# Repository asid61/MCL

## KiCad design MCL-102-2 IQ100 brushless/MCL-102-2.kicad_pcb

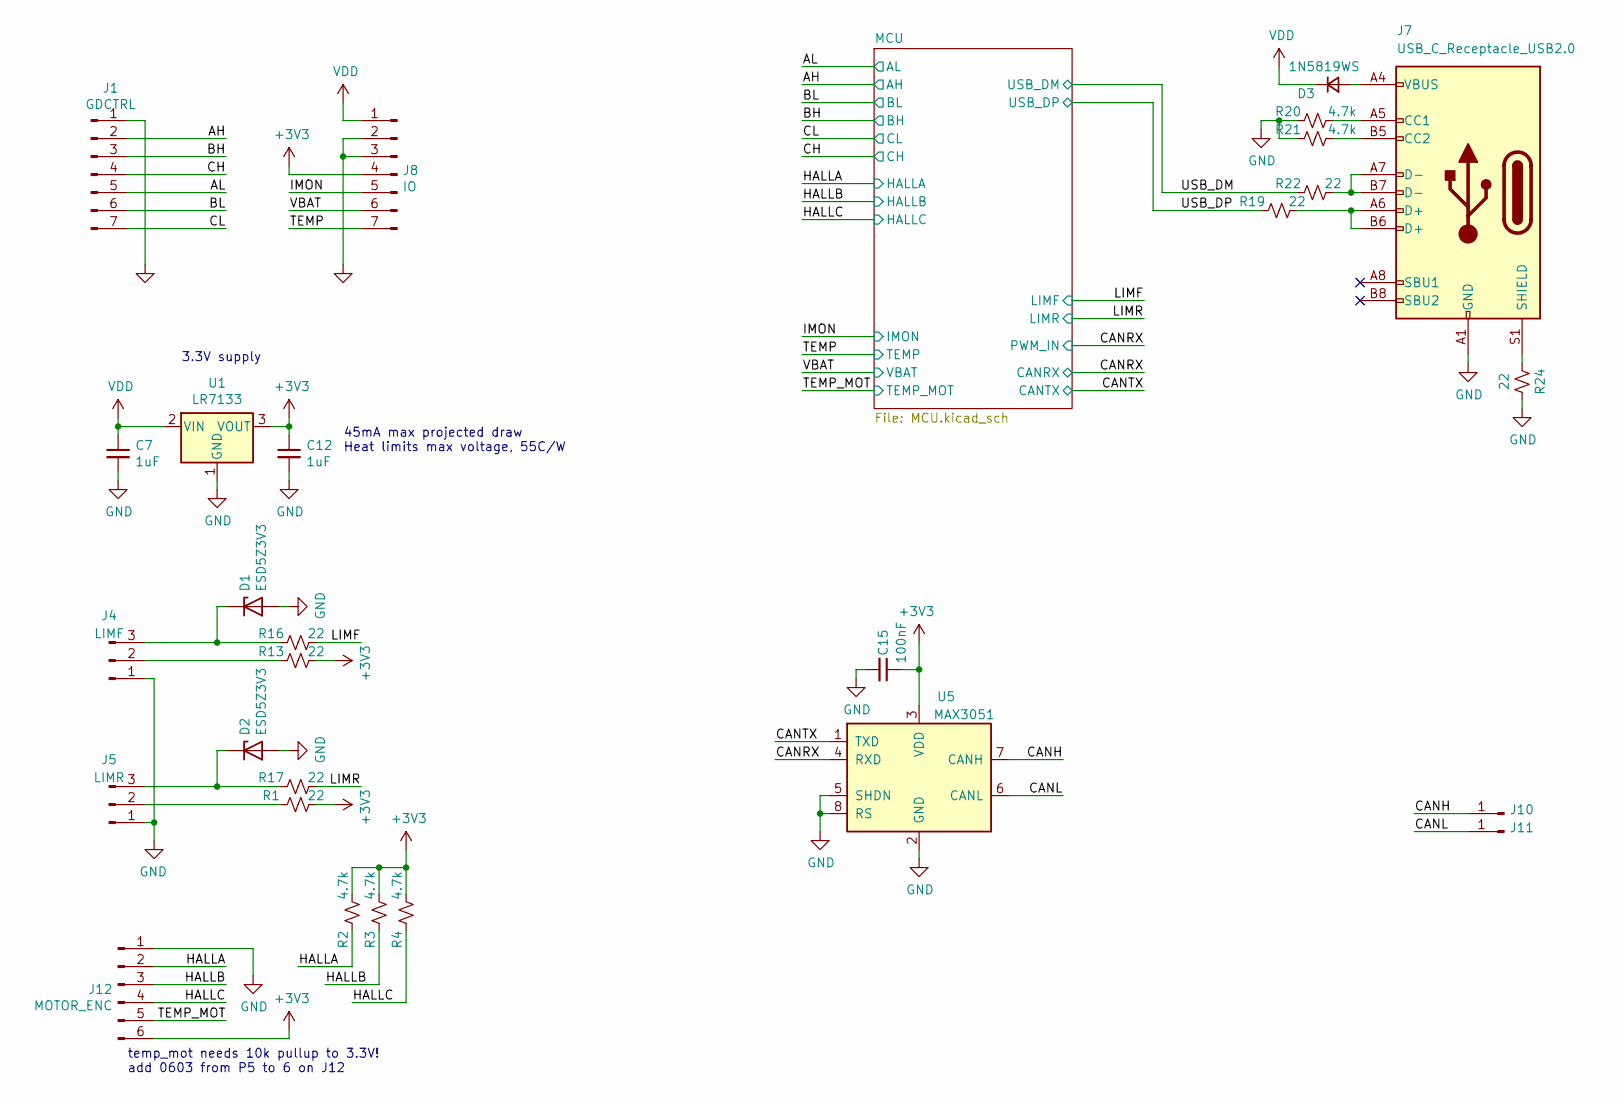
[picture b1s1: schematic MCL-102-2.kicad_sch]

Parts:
C7, C12: 1uF; C_0603_1608Metric; LCSC C15849
C15: 100nF; C_0402_1005Metric
D1, D2: ESD5Z3V3; D_SOD-523; LCSC C502545
D3: 1N5819WS; D_SOD-323; LCSC C191023
J1: GDCTRL; PinSocket_1x07_P2.54mm_Vertical; LCSC C492406
J4: LIMF; PinHeader_1x03_P2.54mm_Horizontal
J5: LIMR; PinHeader_1x03_P2.54mm_Horizontal
J7: USB_C_Receptacle_USB2.0; USB_C_Receptacle_HRO_TYPE-C-31-M-12; LCSC C165948
J8: IO; PinSocket_1x07_P2.54mm_Vertical; LCSC C492406
J10, J11: Conn_01x01_Male; SOLDERPAD_100x200
J12: MOTOR_ENC; JST_PH_S6B-PH-SM4-TB_1x06-1MP_P2.00mm_Horizontal; LCSC C146050
R1, R13, R16, R17, R19, R22, R24: 22; R_0402_1005Metric
R2, R3, R4, R20, R21: 4.7k; R_0402_1005Metric
U1: LR7133; SOT-89-3; LCSC C914127
U5: MAX3051; SOT-23-8; LCSC C112005

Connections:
+3V3: C12.1, C15.1, J8.4, J12.6, R1.2, R2.1, R3.1, R4.1, R13.2, U1.3 (VOUT), U5.3 (VDD); also elsewhere on the board
/AH: J1.2; also elsewhere on the board
/AL: J1.5; also elsewhere on the board
/BH: J1.3; also elsewhere on the board
/BL: J1.6; also elsewhere on the board
/CANH: J10.1, U5.7 (CANH)
/CANL: J11.1, U5.6 (CANL)
/CANRX: U5.4 (RXD); also elsewhere on the board
/CANTX: U5.1 (TXD); also elsewhere on the board
/CH: J1.4; also elsewhere on the board
/CL: J1.7; also elsewhere on the board
/HALLA: J12.2, R2.2; also elsewhere on the board
/HALLB: J12.3, R3.2; also elsewhere on the board
/HALLC: J12.4, R4.2; also elsewhere on the board
/IMON: J8.5; also elsewhere on the board
/LIMF: R16.2; also elsewhere on the board
/LIMR: R17.2; also elsewhere on the board
/TEMP: J8.7; also elsewhere on the board
/TEMP_MOT: J12.5; also elsewhere on the board
/USB_DM: R22.1; also elsewhere on the board
/USB_DP: R19.1; also elsewhere on the board
/VBAT: J8.6; also elsewhere on the board
GND: C7.2, C12.2, C15.2, D1.2 (A), D2.2 (A), J1.1, J4.1, J5.1, J7.A1 (GND), J7.A12 (GND), J7.B1 (GND), J7.B12 (GND), J8.2, J8.3, J12.1, R20.2, R21.2, R24.1, U1.1 (GND), U5.2 (GND), U5.5 (SHDN), U5.8 (RS); also elsewhere on the board
unnamed: D1.1 (K), J4.3, R16.1
unnamed: D2.1 (K), J5.3, R17.1
unnamed: D3.2 (A), J7.A4 (VBUS), J7.A9 (VBUS), J7.B4 (VBUS), J7.B9 (VBUS)
unnamed: J4.2, R13.1
unnamed: J5.2, R1.1
unnamed: J7.A5 (CC1), R20.1
unnamed: J7.A6 (D+), J7.B6 (D+), R19.2
unnamed: J7.A7 (D-), J7.B7 (D-), R22.2
unnamed: J7.B5 (CC2), R21.1
unnamed: J7.S1 (SHIELD), R24.2
VDD: C7.1, D3.1 (K), J8.1, U1.2 (VIN)

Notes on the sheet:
temp_mot needs 10k pullup to 3.3V! add 0603 from P5 to 6 on J12
3.3V supply
45mA max projected draw Heat limits max voltage, 55C/W

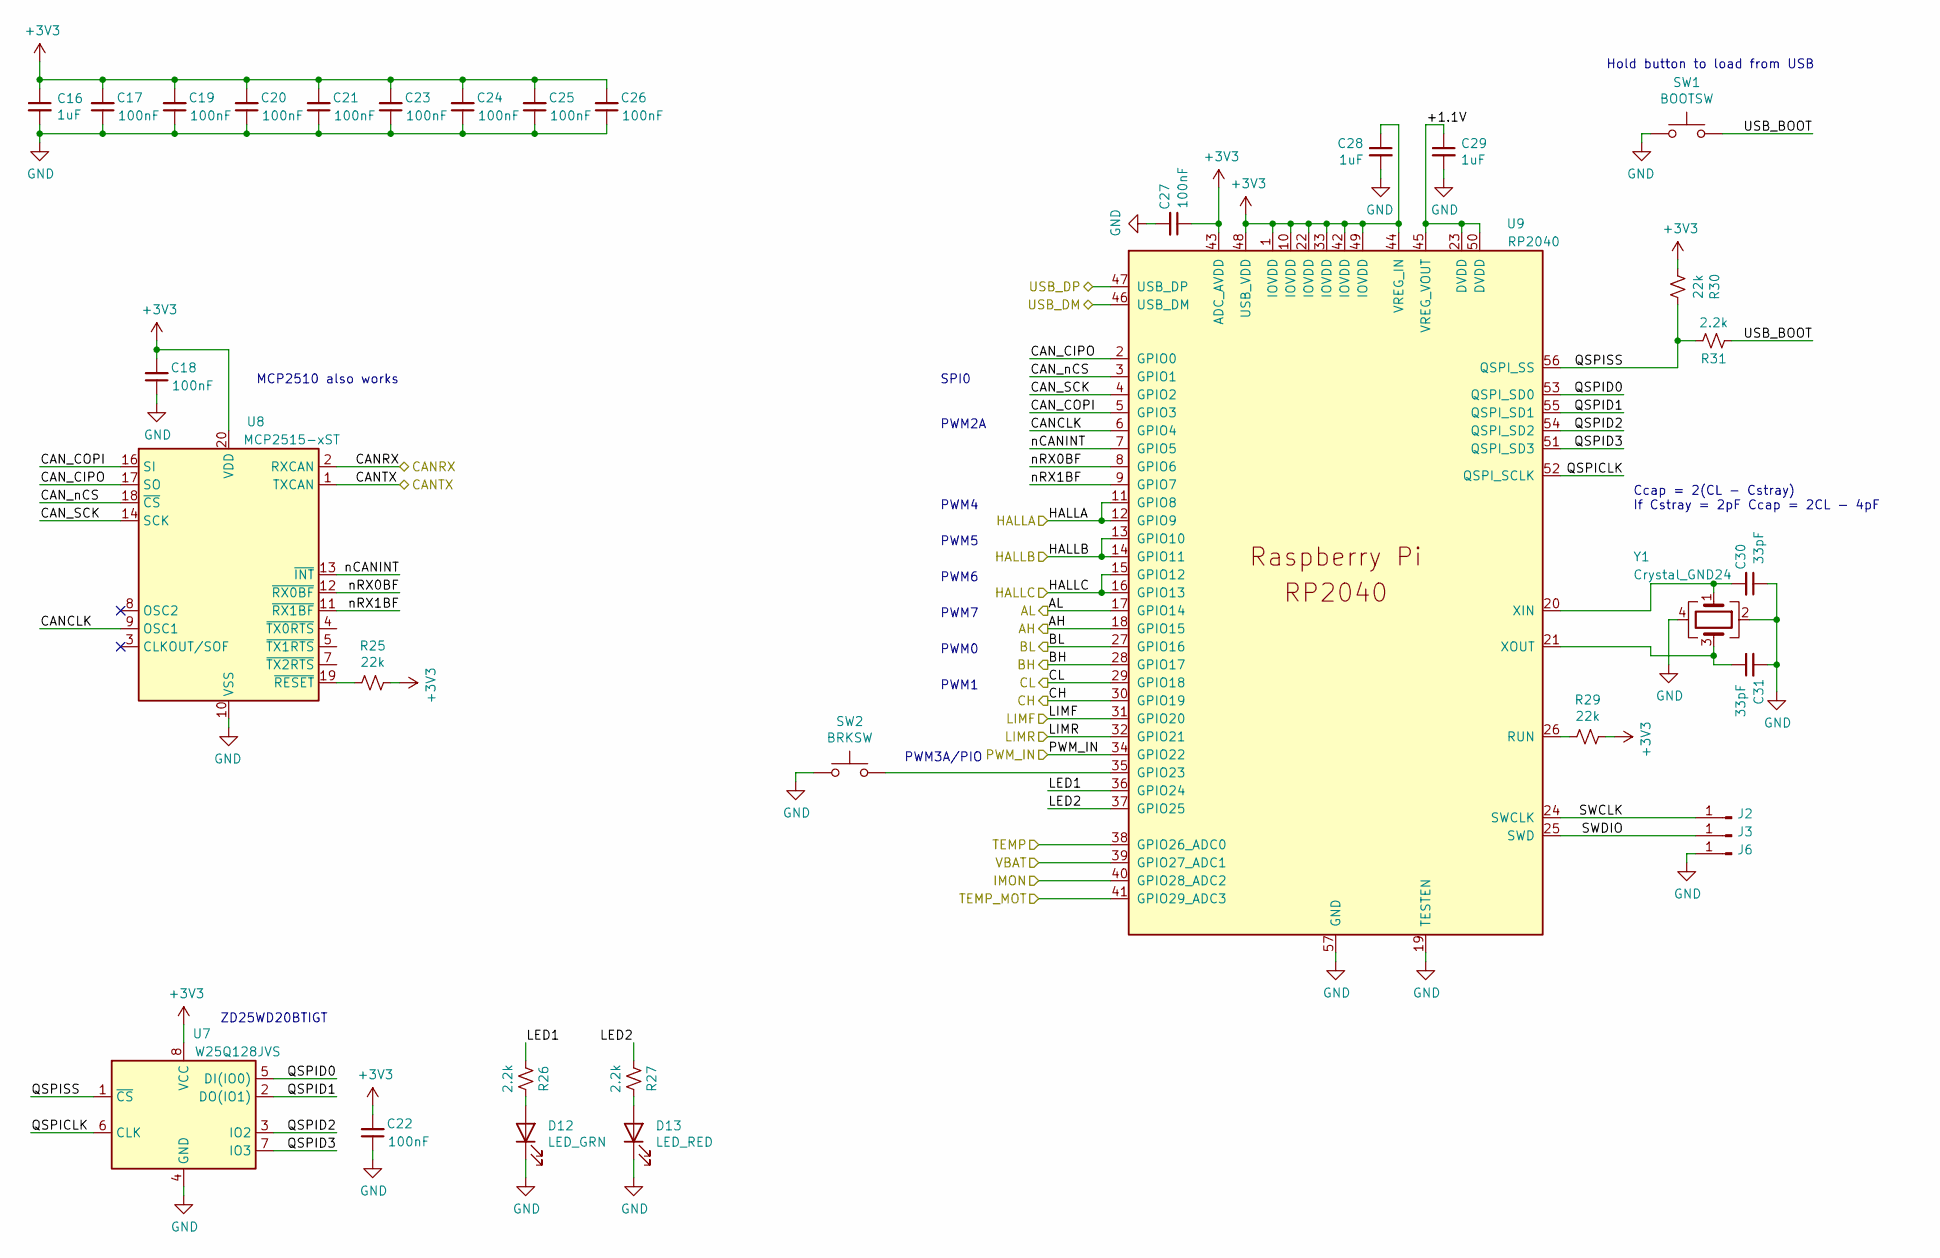
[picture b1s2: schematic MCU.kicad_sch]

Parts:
C16, C28, C29: 1uF; C_0603_1608Metric; LCSC C15849
C17, C18, C19, C20, C21, C22, C23, C24, C25, C26, C27: 100nF; C_0402_1005Metric
C30, C31: 33pF; C_0402_1005Metric
D12: LED_GRN; D_0603_1608Metric
D13: LED_RED; D_0603_1608Metric
J2, J3, J6: Conn_01x01_Male; SOLDERPAD_100x200
R25, R29, R30: 22k; R_0402_1005Metric
R26, R27, R31: 2.2k; R_0402_1005Metric
SW1: BOOTSW; SW_PUSH_6mm_H4.3mm; LCSC C2837531
SW2: BRKSW; SW_PUSH_6mm_H4.3mm; LCSC C2837531
U7: W25Q128JVS; SOIC-8_5.23x5.23mm_P1.27mm; LCSC C97521
U8: MCP2515-xST; TSSOP-20_4.4x6.5mm_P0.65mm; LCSC C185941
U9: RP2040; RP2040-QFN-56; LCSC C2040
Y1: Crystal_GND24; Crystal_SMD_3225-4Pin_3.2x2.5mm; LCSC C9002

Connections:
+3V3: C16.1, C17.2, C18.2, C19.2, C20.2, C21.2, C22.2, C23.2, C24.2, C25.2, C26.2, C27.1, C28.1, R25.2, R29.2, R30.1, U7.8 (VCC), U8.20 (VDD), U9.1 (IOVDD), U9.10 (IOVDD), U9.22 (IOVDD), U9.33 (IOVDD), U9.42 (IOVDD), U9.43 (ADC_AVDD), U9.44 (VREG_IN), U9.48 (USB_VDD), U9.49 (IOVDD); also elsewhere on the board
/AH: U9.18 (GPIO15); also elsewhere on the board
/AL: U9.17 (GPIO14); also elsewhere on the board
/BH: U9.28 (GPIO17); also elsewhere on the board
/BL: U9.27 (GPIO16); also elsewhere on the board
/CANRX: U8.2 (RXCAN), U9.34 (GPIO22); also elsewhere on the board
/CANTX: U8.1 (TXCAN); also elsewhere on the board
/CH: U9.30 (GPIO19); also elsewhere on the board
/CL: U9.29 (GPIO18); also elsewhere on the board
/HALLA: U9.11 (GPIO8), U9.12 (GPIO9); also elsewhere on the board
/HALLB: U9.13 (GPIO10), U9.14 (GPIO11); also elsewhere on the board
/HALLC: U9.15 (GPIO12), U9.16 (GPIO13); also elsewhere on the board
/IMON: U9.40 (GPIO28_ADC2); also elsewhere on the board
/LIMF: U9.31 (GPIO20); also elsewhere on the board
/LIMR: U9.32 (GPIO21); also elsewhere on the board
/MCU/+1.1V: C29.1, U9.23 (DVDD), U9.45 (VREG_VOUT), U9.50 (DVDD)
/MCU/CANCLK: U8.9 (OSC1), U9.6 (GPIO4)
/MCU/CAN_CIPO: U8.17 (SO), U9.2 (GPIO0)
/MCU/CAN_COPI: U8.16 (SI), U9.5 (GPIO3)
/MCU/CAN_SCK: U8.14 (SCK), U9.4 (GPIO2)
/MCU/CAN_nCS: U8.18 (~CS), U9.3 (GPIO1)
/MCU/LED1: R26.2, U9.36 (GPIO24)
/MCU/LED2: R27.2, U9.37 (GPIO25)
/MCU/QSPICLK: U7.6 (CLK), U9.52 (QSPI_SCLK)
/MCU/QSPID0: U7.5 (DI(IO0)), U9.53 (QSPI_SD0)
/MCU/QSPID1: U7.2 (DO(IO1)), U9.55 (QSPI_SD1)
/MCU/QSPID2: U7.3 (IO2), U9.54 (QSPI_SD2)
/MCU/QSPID3: U7.7 (IO3), U9.51 (QSPI_SD3)
/MCU/QSPISS: R30.2, R31.1, U7.1 (~CS), U9.56 (QSPI_SS)
/MCU/SWCLK: J2.1, U9.24 (SWCLK)
/MCU/SWDIO: J3.1, U9.25 (SWD)
/MCU/USB_BOOT: R31.2, SW1.2
/MCU/nCANINT: U8.13 (~INT), U9.7 (GPIO5)
/MCU/nRX0BF: U8.12 (~RX0BF), U9.8 (GPIO6)
/MCU/nRX1BF: U8.11 (~RX1BF), U9.9 (GPIO7)
/TEMP: U9.38 (GPIO26_ADC0); also elsewhere on the board
/TEMP_MOT: U9.41 (GPIO29_ADC3); also elsewhere on the board
/USB_DM: U9.46 (USB_DM); also elsewhere on the board
/USB_DP: U9.47 (USB_DP); also elsewhere on the board
/VBAT: U9.39 (GPIO27_ADC1); also elsewhere on the board
GND: C16.2, C17.1, C18.1, C19.1, C20.1, C21.1, C22.1, C23.1, C24.1, C25.1, C26.1, C27.2, C28.2, C29.2, C30.1, C31.2, D12.1 (K), D13.1 (K), J6.1, SW1.1, SW2.1, U7.4 (GND), U8.10 (VSS), U9.19 (TESTEN), U9.57 (GND), Y1.2, Y1.4; also elsewhere on the board
unnamed: C30.2, U9.20 (XIN), Y1.1
unnamed: C31.1, U9.21 (XOUT), Y1.3
unnamed: D12.2 (A), R26.1
unnamed: D13.2 (A), R27.1
unnamed: R25.1, U8.19 (~RESET)
unnamed: R29.1, U9.26 (RUN)
unnamed: SW2.2, U9.35 (GPIO23)

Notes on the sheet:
Hold button to load from USB
PWM5
PWM7
PWM1
PWM3A/PIO
MCP2510 also works
PWM2A
Ccap = 2(CL - Cstray) If Cstray = 2pF Ccap = 2CL - 4pF
PWM6
ZD25WD20BTIGT
SPI0
PWM0
PWM4

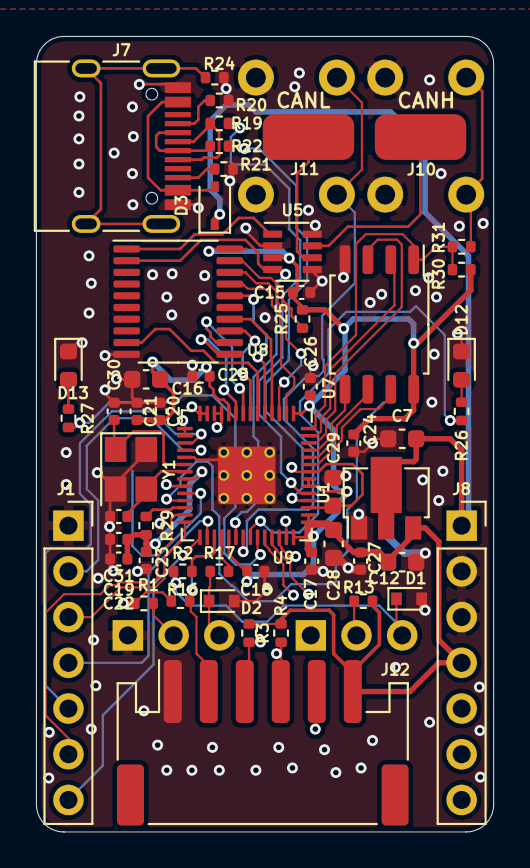
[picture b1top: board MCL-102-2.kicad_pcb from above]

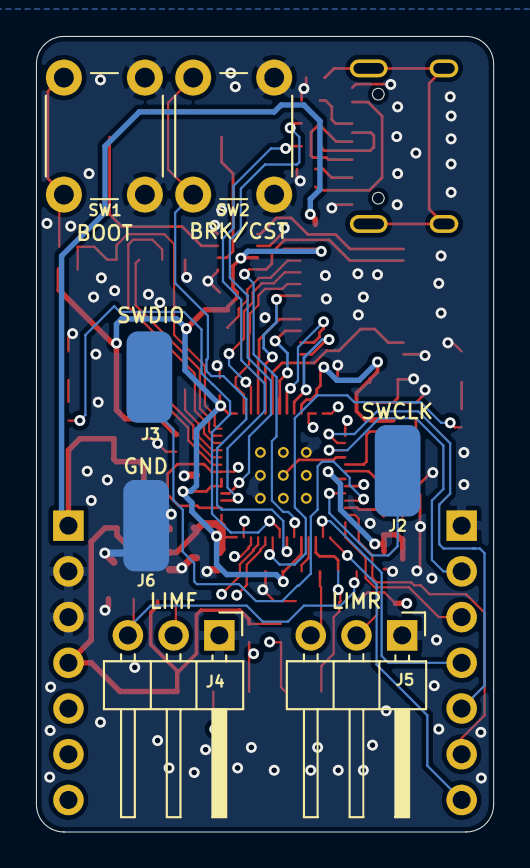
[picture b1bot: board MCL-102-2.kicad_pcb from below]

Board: 4 copper layers, 25.4 x 44.2 mm, 61 parts (7 on the bottom side), 61 nets.

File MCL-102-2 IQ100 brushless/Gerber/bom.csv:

Comment,Designator,Footprint,LCSC
"1uF","C7,C12,C16,C28,C29","Capacitor_SMD:C_0603_1608Metric","C15849"
"100nF","C15,C17,C18,C19,C20,C21,C22,C23,C24,C25,C26,C27","Capacitor_SMD:C_0402_1005Metric",""
"33pF","C30,C31","Capacitor_SMD:C_0402_1005Metric",""
"ESD5Z3V3","D1,D2","Diode_SMD:D_SOD-523","C502545"
"LED_GRN","D12","Diode_SMD:D_0603_1608Metric",""
"LED_RED","D13","Diode_SMD:D_0603_1608Metric",""
"1N5819WS","D3","Diode_SMD:D_SOD-323","C191023"
"GDCTRL","J1","Connector_PinSocket_2.54mm:PinSocket_1x07_P2.54mm_Vertical","C492406"
"Conn_01x01_Male","J2,J3,J6,J10,J11","Anand_parts:SOLDERPAD_100x200",""
"MOTOR_ENC","J12","Connector_JST:JST_PH_S6B-PH-SM4-TB_1x06-1MP_P2.00mm_Horizontal","C146050"
"LIMF","J4","Connector_PinHeader_2.54mm:PinHeader_1x03_P2.54mm_Horizontal",""
"LIMR","J5","Connector_PinHeader_2.54mm:PinHeader_1x03_P2.54mm_Horizontal",""
"USB_C_Receptacle_USB2.0","J7","Connector_USB:USB_C_Receptacle_HRO_TYPE-C-31-M-12","C165948"
"IO","J8","Connector_PinSocket_2.54mm:PinSocket_1x07_P2.54mm_Vertical","C492406"
"4.7k","R2,R3,R4,R20,R21","Resistor_SMD:R_0402_1005Metric",""
"22","R1,R13,R16,R17,R19,R22,R24","Resistor_SMD:R_0402_1005Metric",""
"2.2k","R26,R27,R31","Resistor_SMD:R_0402_1005Metric",""
"22k","R25,R29,R30","Resistor_SMD:R_0402_1005Metric",""
"BOOTSW","SW1","Button_Switch_THT:SW_PUSH_6mm_H4.3mm","C2837531"
"BRKSW","SW2","Button_Switch_THT:SW_PUSH_6mm_H4.3mm","C2837531"
"LR7133","U1","Package_TO_SOT_SMD:SOT-89-3","C914127"
"MAX3051","U5","Package_TO_SOT_SMD:SOT-23-8","C112005"
"W25Q128JVS","U7","Package_SO:SOIC-8_5.23x5.23mm_P1.27mm","C97521"
"MCP2515-xST","U8","Package_SO:TSSOP-20_4.4x6.5mm_P0.65mm","C185941"
"RP2040","U9","MCU_RaspberryPi_and_Boards:RP2040-QFN-56","C2040"
"Crystal_GND24","Y1","Crystal:Crystal_SMD_3225-4Pin_3.2x2.5mm","C9002"

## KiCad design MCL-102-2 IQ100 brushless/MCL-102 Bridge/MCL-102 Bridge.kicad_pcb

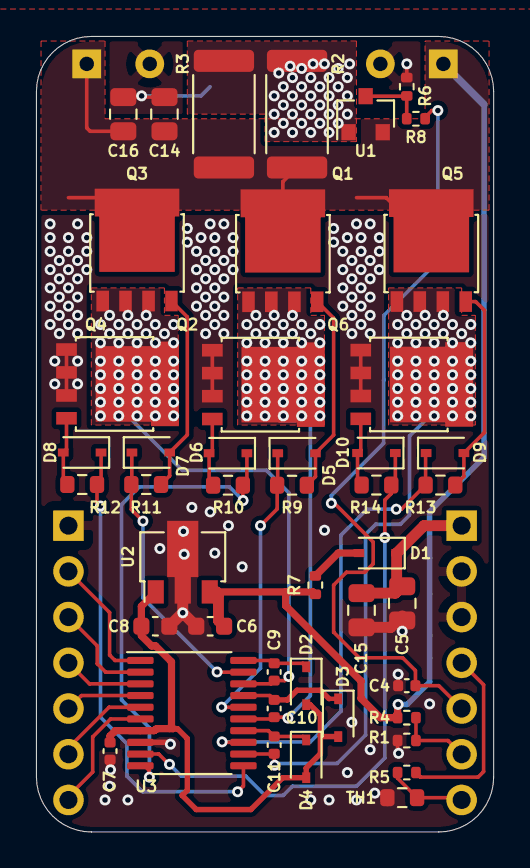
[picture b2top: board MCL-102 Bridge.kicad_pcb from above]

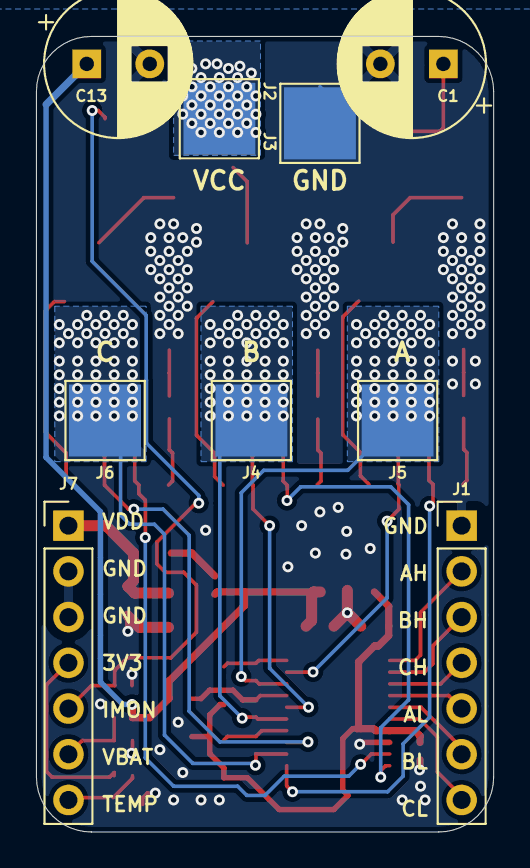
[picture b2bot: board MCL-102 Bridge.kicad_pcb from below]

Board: 4 copper layers, 25.4 x 44.2 mm, 54 parts (9 on the bottom side), 35 nets.

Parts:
C1, C13: 680uF; CP_Radial_D8.0mm_P3.50mm
C4, C7, C9, C10, C11: 100nF; C_0402_1005Metric
C5, C14, C15, C16: 22uF; C_0805_2012Metric
C6, C8: 1uF; C_0603_1608Metric
D1, D2, D3, D4, D5, D6, D7, D8, D9, D10: 1N4148WS; D_SOD-323
J1: GDCTRL; PinHeader_1x07_P2.54mm_Vertical
J2, J3, J4, J5, J6: Conn_01x01_Male; TestPoint_Pad_4.0x4.0mm
J7: IO; PinHeader_1x07_P2.54mm_Vertical
Q1, Q2, Q3, Q4, Q5, Q6: HYG013N03LS1C2; LFPAK56
R1: 4.7k; R_0402_1005Metric
R2, R3: 0.001; R_2512_6332Metric
R4: 22k; R_0402_1005Metric
R5, R6, R8: 2.2k; R_0402_1005Metric
R7: 22; R_0402_1005Metric
R9, R10, R11, R12, R13, R14: 1; R_0603_1608Metric
TH1: 10k; R_0603_1608Metric
U1: ZXCT1009F; SOT-23
U2: L78L12_SOT89; SOT-89-3
U3: EG2133; TSSOP-20_4.4x6.5mm_P0.65mm

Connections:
+3V3: J7.4, R1.2
+12V: C7.2, C8.1, D2.2 (A), D3.2 (A), D4.2 (A), U2.1 (OUT), U3.7 (VCC)
/AH: J1.2, U3.1 (HIN1)
/AHO: D7.1 (K), R11.1, U3.19 (HO1)
/AL: J1.5, U3.4 (~LIN1)
/ALO: D8.1 (K), R12.1, U3.11 (LO1)
/BH: J1.3, U3.2 (HIN2)
/BHO: D5.1 (K), R9.1, U3.16 (HO2)
/BL: J1.6, U3.5 (~LIN2)
/BLO: D6.1 (K), R10.1, U3.10 (LO2)
/CH: J1.4, U3.3 (HIN3)
/CHO: D9.1 (K), R13.1, U3.13 (HO3)
/CL: J1.7, U3.6 (~LIN3)
/CLO: D10.1 (K), R14.1, U3.9 (LO3)
/IMON: C4.2, J7.5, R8.2
/MA: C9.1, J5.1, Q3.1 (S), Q3.2 (S), Q3.3 (S), Q4.5 (D), U3.18 (VS1)
/MB: C10.1, J4.1, Q1.1 (S), Q1.2 (S), Q1.3 (S), Q2.5 (D), U3.15 (VS2)
/MC: C11.1, J6.1, Q5.1 (S), Q5.2 (S), Q5.3 (S), Q6.5 (D), U3.12 (VS3)
/PHASEA/HD: D5.2 (A), Q1.4 (G), R9.2
/PHASEA/LD: D6.2 (A), Q2.4 (G), R10.2
/PHASEB/HD: D7.2 (A), Q3.4 (G), R11.2
/PHASEB/LD: D8.2 (A), Q4.4 (G), R12.2
/Temp: J7.7, R1.1, TH1.1
/VBAT: J7.6, R4.2, R5.1
/sheet6191AFC6/HD: D9.2 (A), Q5.4 (G), R13.2
/sheet6191AFC6/LD: D10.2 (A), Q6.4 (G), R14.2
GND: C1.2, C4.1, C5.2, C6.2, C7.1, C8.2, C13.2, C14.2, C15.2, C16.2, J1.1, J3.1, J7.2, J7.3, Q2.1 (S), Q2.2 (S), Q2.3 (S), Q4.1 (S), Q4.2 (S), Q4.3 (S), Q6.1 (S), Q6.2 (S), Q6.3 (S), R5.2, R6.2, TH1.2, U2.2 (GND), U3.8 (GND)
unnamed: C9.2, D2.1 (K), U3.20 (VB1)
unnamed: C10.2, D3.1 (K), U3.17 (VB2)
unnamed: C11.2, D4.1 (K), U3.14 (VB3)
unnamed: D1.2 (A), R7.2
unnamed: J2.1, R2.1, R3.1, U1.1 (Vs-)
unnamed: R6.1, R8.1, U1.3 (Iout)
VCC: C1.1, C6.1, C13.1, C14.1, C16.1, Q1.5 (D), Q3.5 (D), Q5.5 (D), R2.2, R3.2, R4.1, R7.1, U1.2 (Vs+), U2.3 (IN)
VDD: C5.1, C15.1, D1.1 (K), J7.1

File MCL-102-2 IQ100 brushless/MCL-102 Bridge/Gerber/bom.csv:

Comment,Designator,Footprint,LCSC
"680uF","C1,C13","Capacitor_THT:CP_Radial_D8.0mm_P3.50mm","C442829"
"100nF","C4,C7,C9,C10,C11","Capacitor_SMD:C_0402_1005Metric",""
"22uF","C5,C14,C15,C16","Capacitor_SMD:C_0805_2012Metric","C45783"
"1uF","C6,C8","Capacitor_SMD:C_0603_1608Metric","C15849"
"1N4148WS","D1,D2,D3,D4,D5,D6,D7,D8,D9,D10","Diode_SMD:D_SOD-323","C2128"
"Conn_01x08_Male","IO1","Connector_PinHeader_2.54mm:PinHeader_1x07_P2.54mm_Vertical",""
"GDCTRL","J1","Connector_PinHeader_2.54mm:PinHeader_1x07_P2.54mm_Vertical",""
"Conn_01x01_Male","J2,J3,J4,J5,J6","TestPoint:TestPoint_Pad_4.0x4.0mm",""
"HYG013N03LS1C2","Q1,Q2,Q3,Q4,Q5,Q6","Package_TO_SOT_SMD:LFPAK56","C2763405"
"4.7k","R1","Resistor_SMD:R_0402_1005Metric",""
"1","R9,R10,R11,R12,R13,R14","Resistor_SMD:R_0603_1608Metric","C22936"
"0.001","R2,R3","Resistor_SMD:R_2512_6332Metric",""
"22k","R4","Resistor_SMD:R_0402_1005Metric",""
"2.2k","R5,R6,R8","Resistor_SMD:R_0402_1005Metric",""
"22","R7","Resistor_SMD:R_0402_1005Metric",""
"10k","TH1","Resistor_SMD:R_0603_1608Metric",""
"ZXCT1009F","U1","Package_TO_SOT_SMD:SOT-23",""
"L78L12_SOT89","U2","Package_TO_SOT_SMD:SOT-89-3","C347258"
"EG2133","U3","Package_SO:TSSOP-20_4.4x6.5mm_P0.65mm",""

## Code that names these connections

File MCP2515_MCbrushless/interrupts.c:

#include "interrupts.h"


void gpio_interrupt_callback(uint gpio, uint32_t events) {
    if(gpio == HALLA || gpio == HALLB || gpio == HALLC) {
        brushless_commutation_callback(false);
    }
}

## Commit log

2025-02-04 add code from old stuff
2025-07-22 add PCBA
